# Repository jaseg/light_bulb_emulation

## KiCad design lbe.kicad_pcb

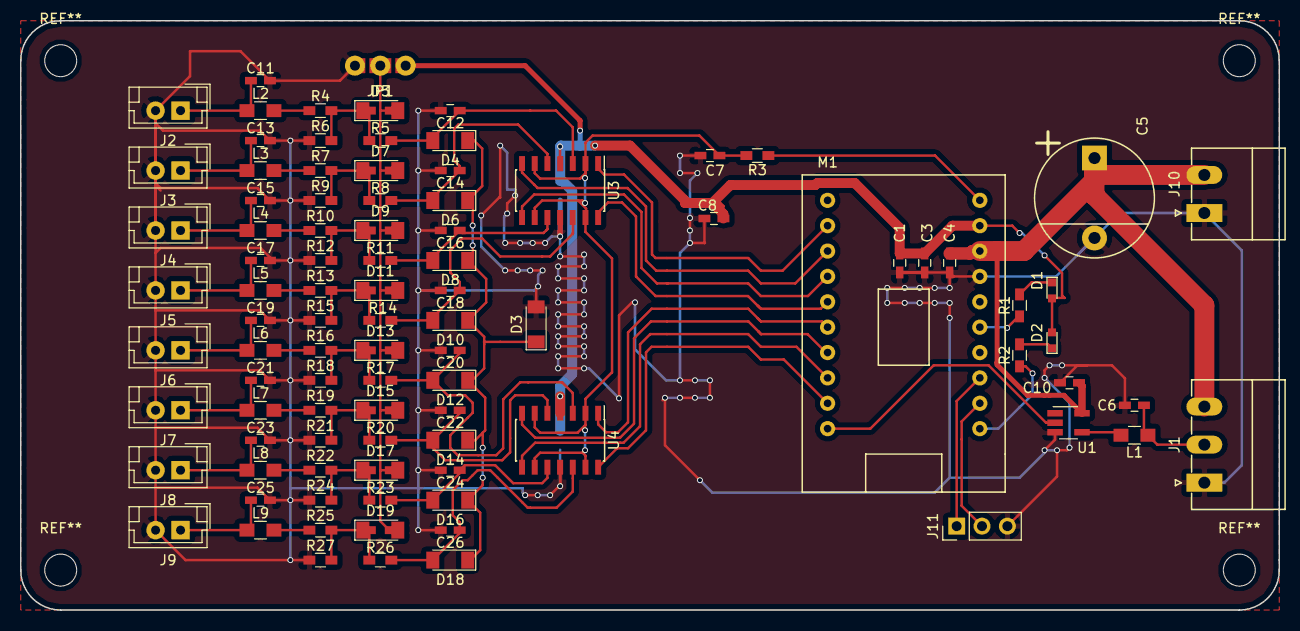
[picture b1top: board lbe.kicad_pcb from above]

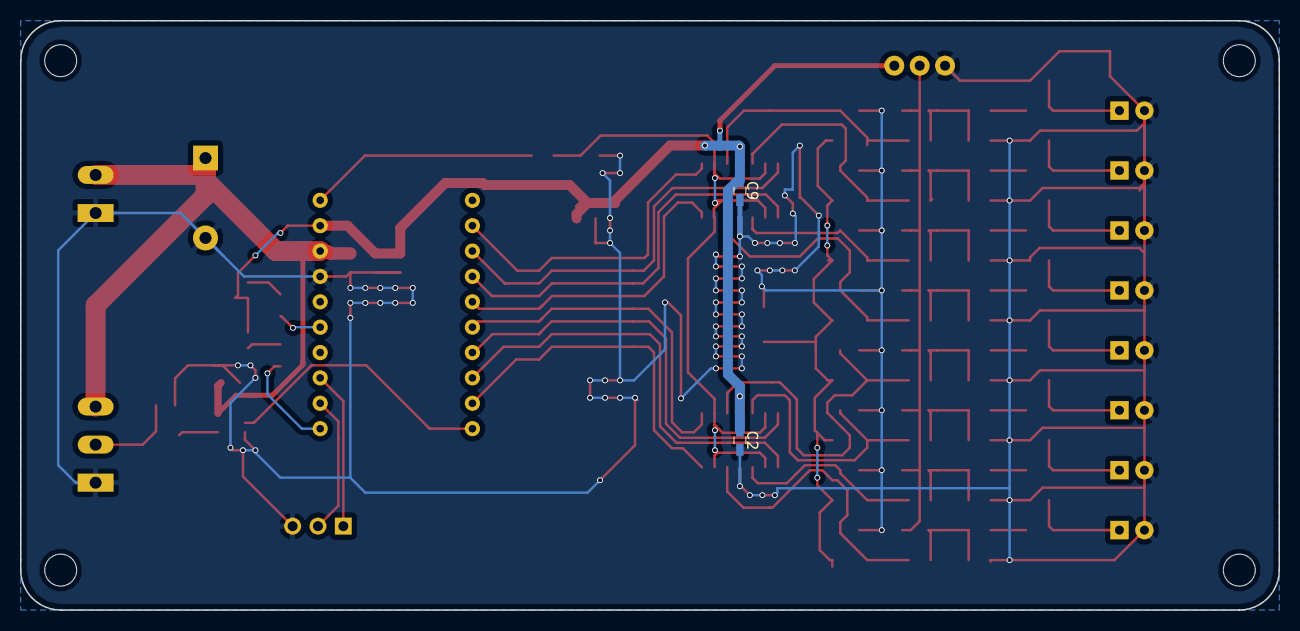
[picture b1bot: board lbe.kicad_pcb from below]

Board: 2 copper layers, 126.0 x 59.0 mm, 97 parts (2 on the bottom side), 56 nets.

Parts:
C1, C4: 10u; C_0603_HandSoldering
C2, C3, C8, C9, C10: 100n; C_0603_HandSoldering
C5: 1000u; Cap_electrolytic_8x10
C6: 10p; C_0603_HandSoldering
C7: 10n; C_0603_HandSoldering
C11, C12, C13, C14, C15, C16, C17, C18, C19, C20, C21, C22, C23, C24, C25, C26: 47n; C_0603_HandSoldering
D1: LED1 (gn); LED_0603
D2: LED2 (rd); LED_0603
D3: D_Zener_Small_ALT; D_MiniMELF_Standard
D4, D6, D8, D10, D12, D14, D16, D18: 4142; D_MiniMELF_Standard
D5, D7, D9, D11, D13, D15, D17, D19: 4142; MiniMelf_0603_combo
J1: Screw_Terminal_1x03; PhoenixContact_MC-G_03x3.81mm_Angled
J2, J3, J4, J5, J6, J7, J8, J9: IN; JST_EH_B02B-EH-A_02x2.50mm_Straight
J10: Screw_Terminal_1x02; PhoenixContact_MC-G_02x3.81mm_Angled
J11: CONN_01X03; Pin_Header_Straight_1x03_Pitch2.54mm
JP1: jumper_nc_no_dual; Header_with_SMD_jumper_1x3_2.54
L1, L2, L3, L4, L5, L6, L7, L8, L9: Ferrite_Bead_Small; R_0805_HandSoldering
M1: BLUEPILL_STM8S103F3
R1: 100; R_0603_HandSoldering
R2: 120; R_0603_HandSoldering
R3, R6, R9, R12, R15, R18, R21, R24, R27: 4k7; R_0603_HandSoldering
R4, R7, R10, R13, R16, R19, R22, R25: 22k; R_0603_HandSoldering
R5, R8, R11, R14, R17, R20, R23, R26: 47k; R_0603_HandSoldering
U1: SN74LV1T34; SOT-23-5_HandSoldering
U3, U4: MCP6004; SOIC-14_3.9x8.7mm_Pitch1.27mm

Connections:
+5V: C4.1, C5.1, C10.1, J1.3, J10.2, M1.8, U1.5
/D0: M1.12, U3.1
/D1: M1.13, U3.7
/D2: M1.14, U3.8
/D3: M1.15, U3.14
/D4: M1.16, U4.1
/D5: M1.17, U4.7
/D6: M1.18, U4.8
/D7: M1.19, U4.14
/LED1: M1.5, R1.2
/LED2: M1.1, R2.2
/LED_OUT: M1.20, U1.2
/RX: J11.1, M1.3
/THR_PWM: M1.10, R3.1
/TX: J11.2, M1.2
/input_group0/Vref: C7.1, R3.2, U3.2, U3.6, U3.9, U3.13, U4.2, U4.6, U4.9, U4.13
/input_group0/sheet5AD30D18/Vclamp: D5.2, D7.2, D9.2, D11.2, D13.2, D15.2, D17.2, D19.2, JP1.2
GND: C1.2, C2.2, C3.2, C4.2, C5.2, C6.2, C7.2, C8.2, C9.2, C10.2, C11.2, C12.2, C13.2, C14.2, C15.2, C16.2, C17.2, C18.2, C19.2, C20.2, C21.2, C22.2, C23.2, C24.2, C25.2, C26.2, D3.2, J1.1, J2.2, J3.2, J4.2, J5.2, J6.2, J7.2, J8.2, J9.2, J10.1, J11.3, JP1.1, M1.7, R6.1, R9.1, R12.1, R15.1, R18.1, R21.1, R24.1, R27.1, U1.3, U3.11, U4.11
unnamed: C6.1, J1.2, L1.1
unnamed: C11.1, J2.1, L2.1
unnamed: C12.1, D4.2, R5.2, U3.3
unnamed: C13.1, J3.1, L3.1
unnamed: C14.1, D6.2, R8.2, U3.5
unnamed: C15.1, J4.1, L4.1
unnamed: C16.1, D8.2, R11.2, U3.10
unnamed: C17.1, J5.1, L5.1
unnamed: C18.1, D10.2, R14.2, U3.12
unnamed: C19.1, J6.1, L6.1
unnamed: C20.1, D12.2, R17.2, U4.3
unnamed: C21.1, J7.1, L7.1
unnamed: C22.1, D14.2, R20.2, U4.5
unnamed: C23.1, J8.1, L8.1
unnamed: C24.1, D16.2, R23.2, U4.10
unnamed: C25.1, J9.1, L9.1
unnamed: C26.1, D18.2, R26.2, U4.12
unnamed: D1.1, R1.1
unnamed: D2.1, R2.1
unnamed: D5.1, R4.2, R5.1, R6.2
unnamed: D7.1, R7.2, R8.1, R9.2
unnamed: D9.1, R10.2, R11.1, R12.2
unnamed: D11.1, R13.2, R14.1, R15.2
unnamed: D13.1, R16.2, R17.1, R18.2
unnamed: D15.1, R19.2, R20.1, R21.2
unnamed: D17.1, R22.2, R23.1, R24.2
unnamed: D19.1, R25.2, R26.1, R27.2
unnamed: L1.2, U1.4
unnamed: L2.2, R4.1
unnamed: L3.2, R7.1
unnamed: L4.2, R10.1
unnamed: L5.2, R13.1
unnamed: L6.2, R16.1
unnamed: L7.2, R19.1
unnamed: L8.2, R22.1
unnamed: L9.2, R25.1
VCOM: D3.1, D4.1, D6.1, D8.1, D10.1, D12.1, D14.1, D16.1, D18.1
VDD: C1.1, C2.1, C3.1, C8.1, C9.1, D1.2, D2.2, JP1.3, M1.9, U3.4, U4.4

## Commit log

2018-04-14 Layout complete
2018-04-14 Add pullup option
2018-04-14 8ch version without buffer
2018-04-14 Add serial header, restore holes
